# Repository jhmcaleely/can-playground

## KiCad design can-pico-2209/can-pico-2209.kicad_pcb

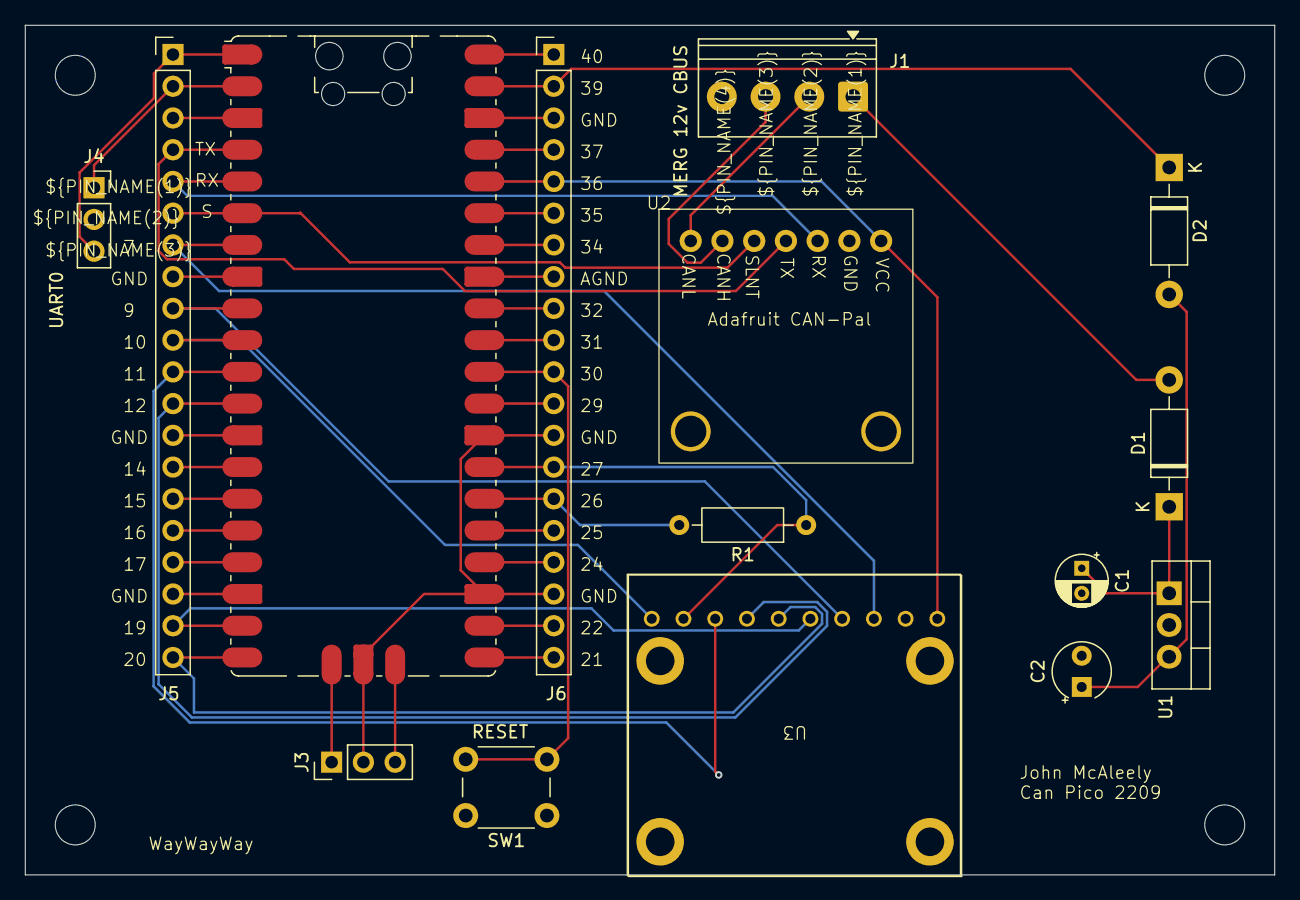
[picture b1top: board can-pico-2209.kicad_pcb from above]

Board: 2 copper layers, 100.0 x 68.0 mm, 19 parts (0 on the bottom side), 41 nets.

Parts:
A1: RaspberryPi_Pico; RaspberryPi_Pico_SMD_HandSolder
C1: 100uF, 25V; CP_Radial_D4.0mm_P2.00mm
C2: 4.7uF; CP_Radial_Tantal_D4.5mm_P2.50mm
D1: 1N4002; D_DO-41_SOD81_P10.16mm_Horizontal
D2: 1N5817; D_DO-41_SOD81_P10.16mm_Horizontal
H1, H2, H3, H4: MountingHole; MountingHole_3.2mm_M3
J1: MERG 12v CBUS; TerminalBlock_Phoenix_PT-1,5-4-3.5-H_1x04_P3.50mm_Horizontal
J3: DEBUG; PinHeader_1x03_P2.54mm_Vertical
J4: UART0; PinSocket_1x03_P2.54mm_Vertical
J5: Pico LHS; PinHeader_1x20_P2.54mm_Vertical
J6: Pico RHS; PinHeader_1x20_P2.54mm_Vertical
R1: 1K; R_Axial_DIN0207_L6.3mm_D2.5mm_P10.16mm_Horizontal
SW1: RESET; SW_PUSH_6mm
U1: LM7805_TO220; TO-220-3_Vertical
U2: Can-Pal; CAN-Pal
U3: Adafruit 2209

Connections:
GND: A1.3 (GND_IN), A1.8 (GND), A1.13 (GND), A1.18 (GND), A1.23 (GND), A1.28 (GND), A1.38 (GND), A1.D2 (GND), C1.2, C2.2, J1.4 (CAN_0v), J3.2 (GND), J4.2 (GND), J5.3, J5.8, J5.13, J5.18, J6.3, J6.13, J6.18, SW1.1, U1.2 (GND), U2.6 (GND), U3.2 (GND)
unnamed: A1.36 (3V3), J6.5, U2.7 (VCC), U3.1 (VDD)
unnamed: A1.37 (3V3_EN), J6.4
unnamed: A1.35 (ADC_VREF), J6.6
unnamed: A1.33 (AGND), J6.8
unnamed: A1.1 (UART0_TX), J4.3 (TX), J5.1
unnamed: A1.2 (UART0_RX), J4.1 (RX), J5.2
unnamed: A1.4 (GPIO2), J5.4, U2.4 (TX)
unnamed: A1.5 (GPIO3), J5.5, U2.5 (RX)
unnamed: A1.6 (GPIO4), J5.6, U2.3 (SLNT)
unnamed: A1.7 (GPIO5), J5.7, U3.3 (DIR)
unnamed: A1.9 (GPIO6), J5.9, U3.4 (STEP)
unnamed: A1.10 (GPIO7), J5.10, U3.10 (EN)
unnamed: A1.11 (GPIO8), J5.11, U3.8 (INDEX)
unnamed: A1.12 (GPIO9), J5.12, U3.7 (DIAG)
unnamed: A1.14 (GPIO10), J5.14
unnamed: A1.15 (GPIO11), J5.15
unnamed: A1.16 (GPIO12), J5.16
unnamed: A1.17 (GPIO13), J5.17
unnamed: A1.19 (GPIO14), J5.19, U3.5 (MS1)
unnamed: A1.20 (GPIO15), J5.20, U3.6 (MS2)
unnamed: A1.21 (GPIO16), J6.20
unnamed: A1.22 (GPIO17), J6.19
unnamed: A1.24 (GPIO18), J6.17
unnamed: A1.25 (GPIO19), J6.16
unnamed: A1.26 (UART1_TX), J6.15, R1.2
unnamed: A1.27 (UART1_RX), J6.14, R1.1, U3.9 (UART)
unnamed: A1.29 (GPIO22), J6.12
unnamed: A1.31 (GPIO26_ADC0), J6.10
unnamed: A1.32 (GPIO27_ADC1), J6.9
unnamed: A1.34 (GPIO28_ADC2), J6.7
unnamed: A1.30 (RUN), J6.11, SW1.2
unnamed: A1.D1 (SWCLK), J3.1 (SWCLK)
unnamed: A1.D3 (SWDIO), J3.3 (SWDIO)
unnamed: A1.40 (VBUS), J6.1 (VBUS)
unnamed: A1.39 (VSYS), D2.1 (K), J6.2
unnamed: D1.2 (A), J1.1 (+12v)
unnamed: C1.1, D1.1 (K), U1.1 (VI)
unnamed: C2.1, D2.2 (A), U1.3 (VO)
unnamed: J1.3 (CANH), U2.2 (CANH)
unnamed: J1.2 (CANL), U2.1 (CANL)
